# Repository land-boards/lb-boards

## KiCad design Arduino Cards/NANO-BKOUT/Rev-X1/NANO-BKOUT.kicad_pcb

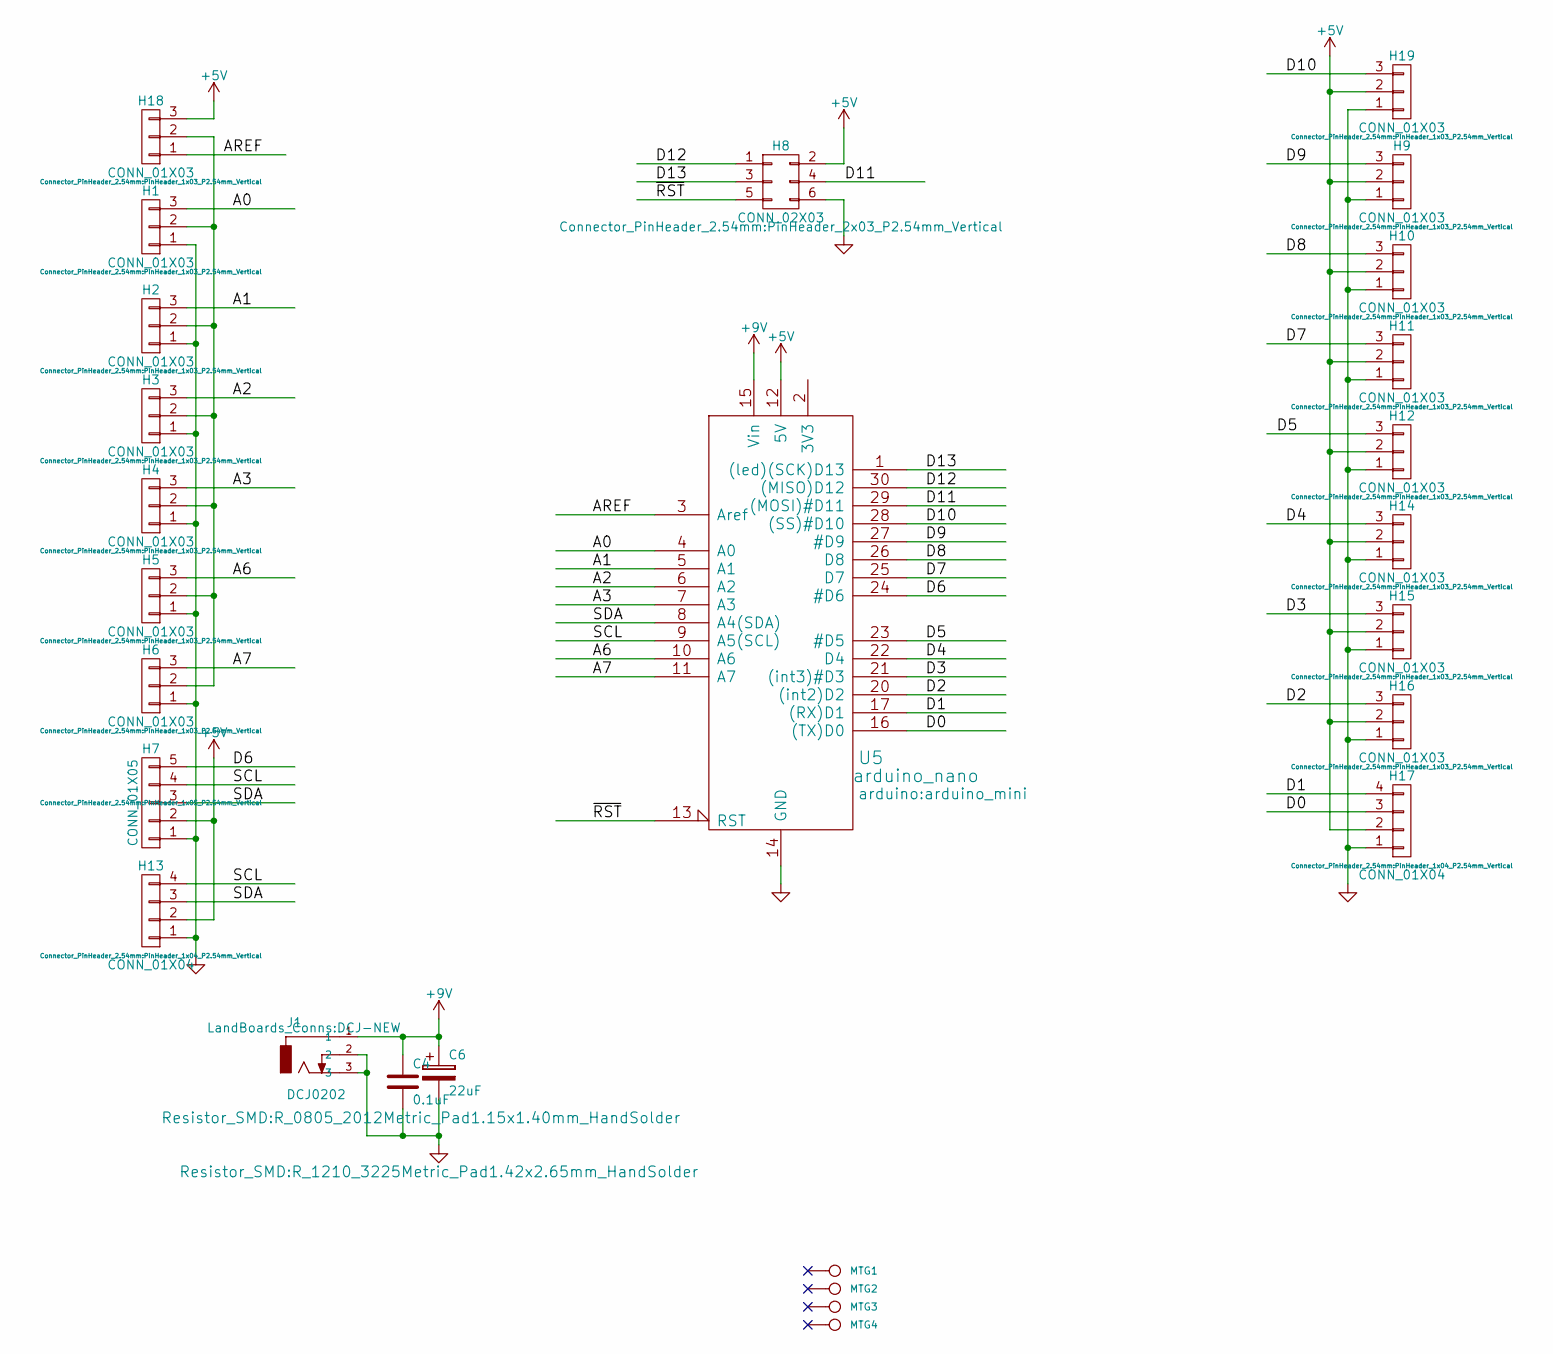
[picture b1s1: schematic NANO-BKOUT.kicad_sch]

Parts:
C4: 0.1uF; R_0805_2012Metric_Pad1.15x1.40mm_HandSolder
C6: 22uF; R_1210_3225Metric_Pad1.42x2.65mm_HandSolder
H1, H2, H3, H4, H5, H6, H9, H10, H11, H12, H14, H15, H16, H18, H19: CONN_01X03; PinHeader_1x03_P2.54mm_Vertical
H7: CONN_01X05; PinHeader_1x05_P2.54mm_Vertical
H8: CONN_02X03; PinHeader_2x03_P2.54mm_Vertical
H13, H17: CONN_01X04; PinHeader_1x04_P2.54mm_Vertical
J1: DCJ0202; DCJ-NEW
MTG1, MTG2, MTG3, MTG4: CONN_1; MTG-4-40
U5: arduino_nano; arduino_mini

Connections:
+5V: H7.2, H8.2, H9.2, H10.2, H11.2, H12.2, H13.2, H14.2, H15.2, H16.2, H17.2, H18.3, H19.2, U5.12 (5V)
+9V: C4.1, C6.1, J1.1, U5.15 (Vin)
/A0: H1.3, U5.4 (A0)
/A1: H2.3, U5.5 (A1)
/A2: H3.3, U5.6 (A2)
/A3: H4.3, U5.7 (A3)
/A6: H5.3, U5.10 (A6)
/A7: H6.3, U5.11 (A7)
/AREF: H18.1, U5.3 (Aref)
/D0: H17.3, U5.16 ((TX)D0)
/D1: H17.4, U5.17 ((RX)D1)
/D2: H16.3, U5.20 ((int2)D2)
/D3: H15.3, U5.21 ((int3)#D3)
/D4: H14.3, U5.22 (D4)
/D5: H12.3, U5.23 (#D5)
/D6: H7.5, U5.24 (#D6)
/D7: H11.3, U5.25 (D7)
/D8: H10.3, U5.26 (D8)
/D9: H9.3, U5.27 (#D9)
/D10: H19.3, U5.28 ((SS)#D10)
/D11: H8.4, U5.29 ((MOSI)#D11)
/D12: H8.1, U5.30 ((MISO)D12)
/D13: H8.3, U5.1 ((led)(SCK)D13)
/SCL: H7.4, H13.4, U5.9 (A5(SCL))
/SDA: H7.3, H13.3, U5.8 (A4(SDA))
/~RST: H8.5, U5.13 (RST)
GND: C4.2, C6.2, H1.1, H2.1, H3.1, H4.1, H5.1, H6.1, H7.1, H8.6, H9.1, H10.1, H11.1, H12.1, H13.1, H14.1, H15.1, H16.1, H17.1, H19.1, J1.2, J1.3, U5.14 (GND), U5.19 (GND)
unnamed: H1.2, H2.2, H3.2, H4.2, H5.2, H6.2, H18.2

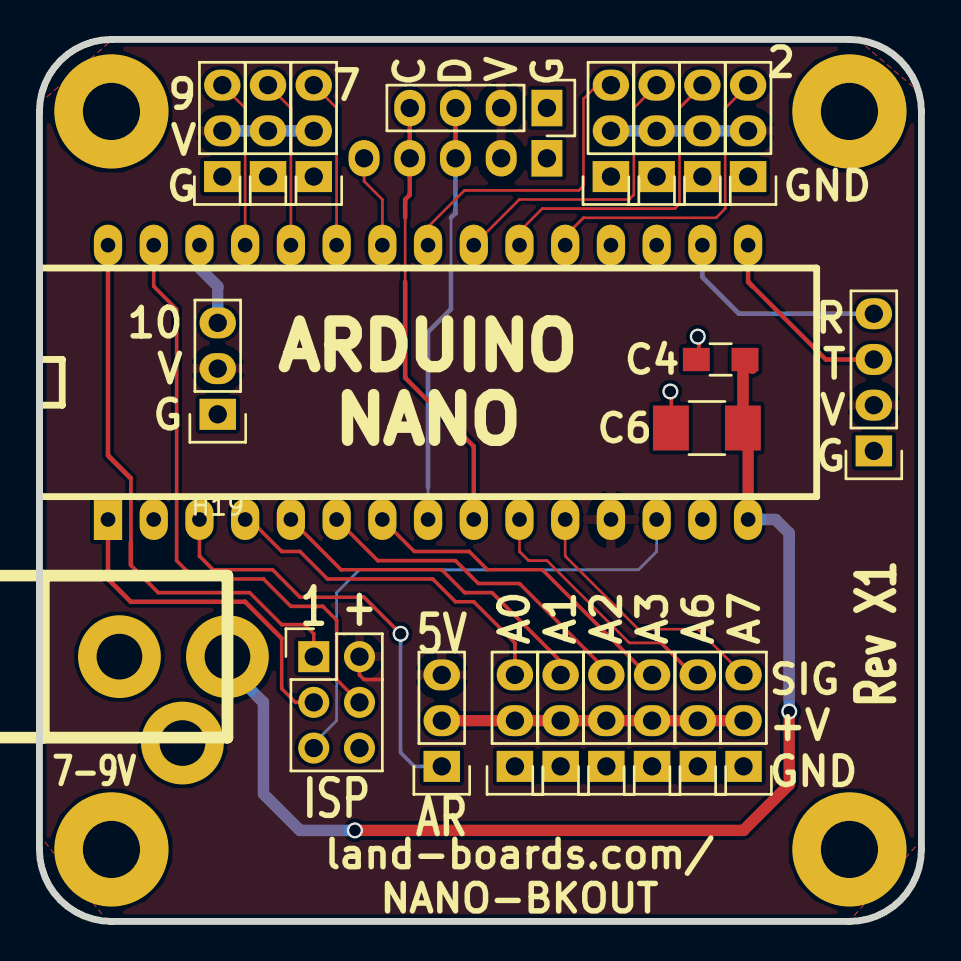
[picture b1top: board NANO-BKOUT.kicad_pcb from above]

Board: 2 copper layers, 49.0 x 49.0 mm, 27 parts (1 on the bottom side), 28 nets.

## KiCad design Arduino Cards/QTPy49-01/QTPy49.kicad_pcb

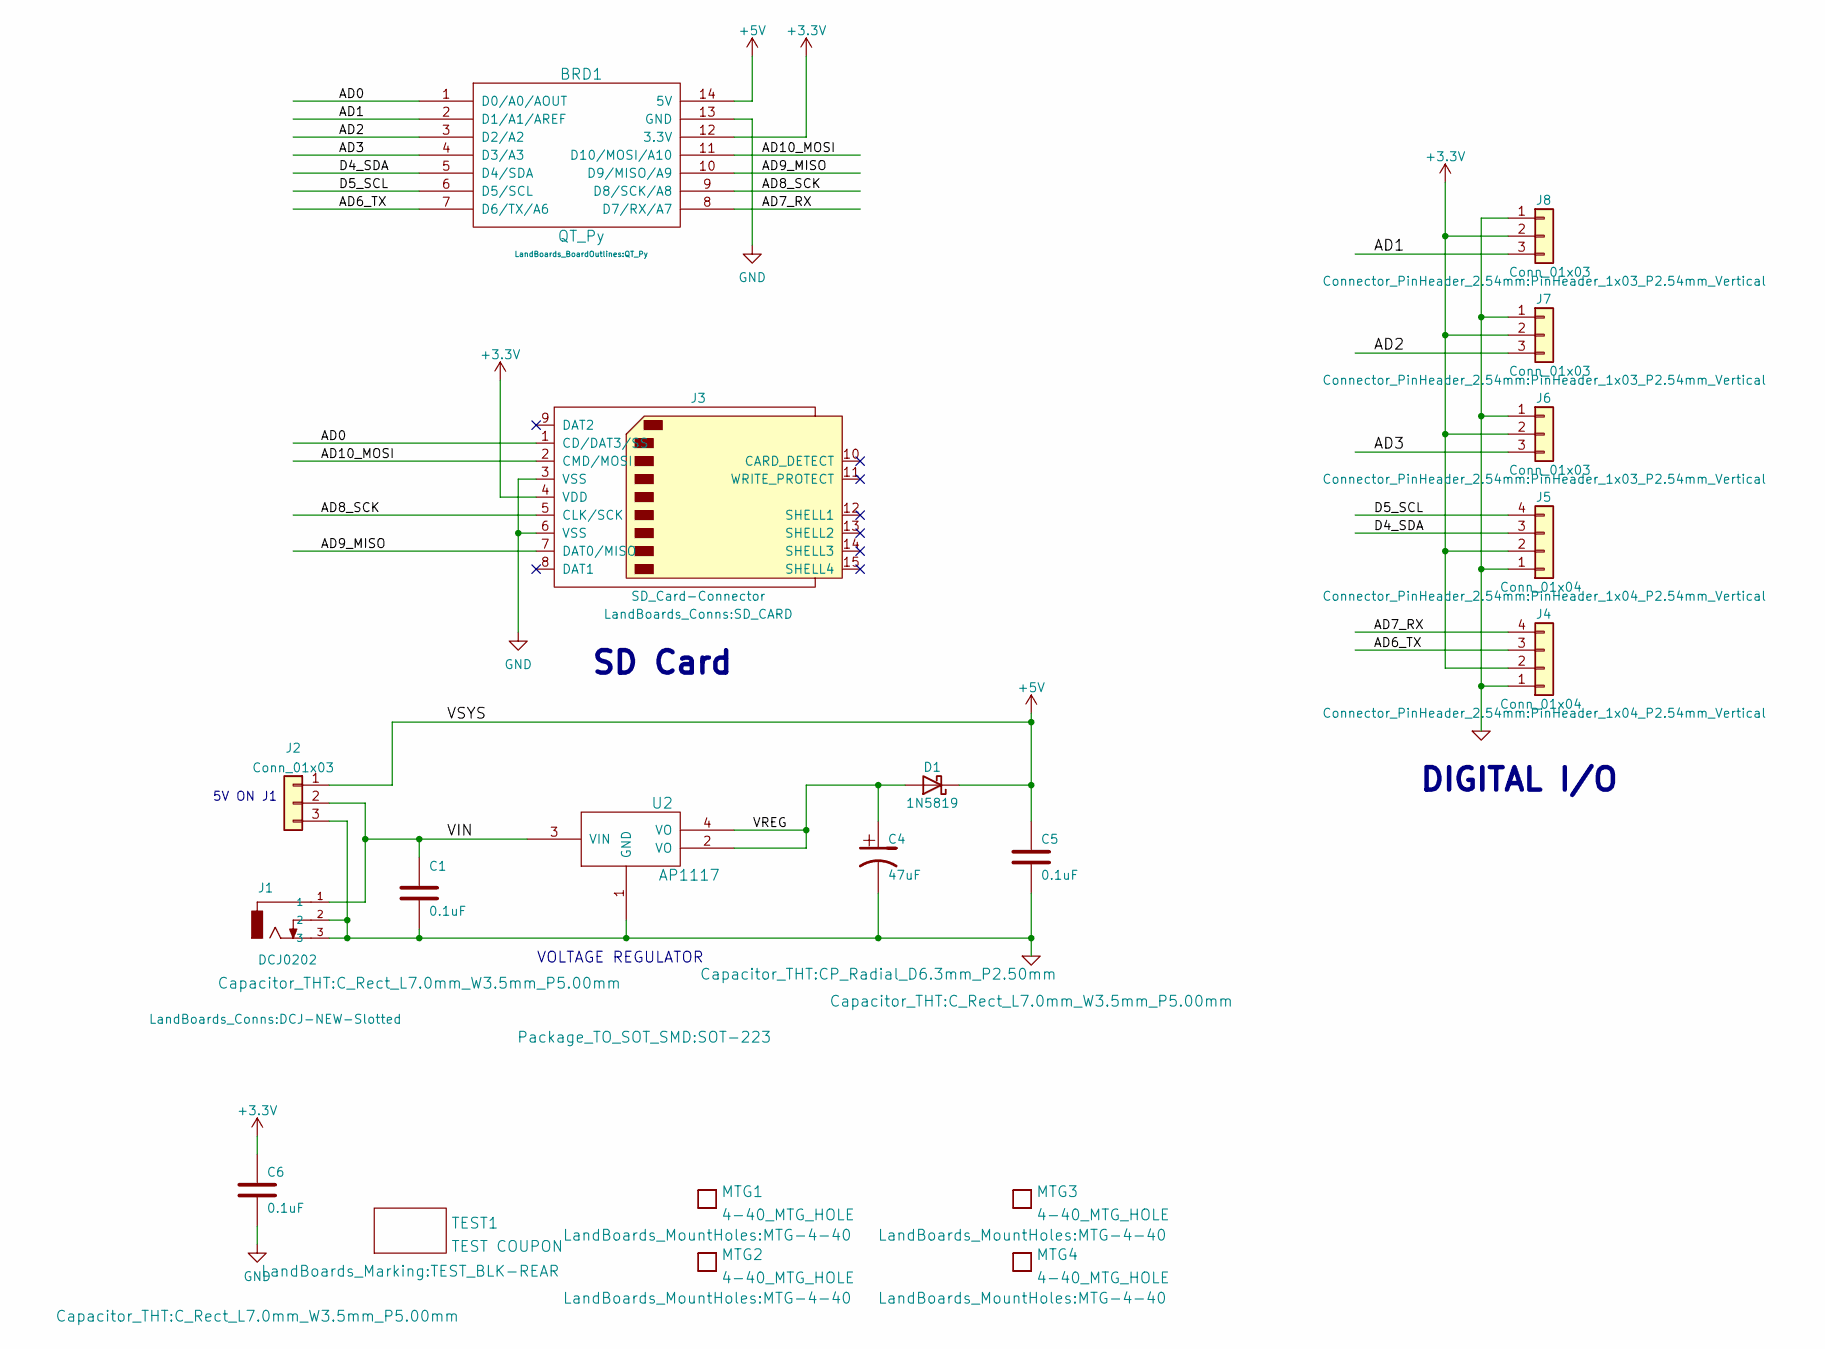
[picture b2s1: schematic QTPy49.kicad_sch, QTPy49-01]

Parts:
BRD1: QT_Py
C1, C5, C6: 0.1uF; C_Rect_L7.0mm_W3.5mm_P5.00mm
C4: 47uF; CP_Radial_D6.3mm_P2.50mm
D1: 1N5819; D_DO-41_SOD81_P10.16mm_Horizontal
J1: DCJ0202; DCJ-NEW-Slotted
J2, J6, J7, J8: Conn_01x03; PinHeader_1x03_P2.54mm_Vertical
J3: SD_Card-Connector; SD_CARD
J4, J5: Conn_01x04; PinHeader_1x04_P2.54mm_Vertical
MTG1, MTG2, MTG3, MTG4: 4-40_MTG_HOLE; MTG-4-40
TEST1: TEST COUPON; TEST_BLK-REAR
U2: AP1117; SOT-223

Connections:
+3V3: BRD1.12 (3.3V), C6.1, J3.4 (VDD), J4.2, J5.2, J6.2, J7.2, J8.2
+5V: BRD1.14 (5V), C5.1, D1.1 (K), J2.1
/AD0: BRD1.1 (D0/A0/AOUT), J3.1 (CD/DAT3/SS)
/AD1: BRD1.2 (D1/A1/AREF), J8.3
/AD2: BRD1.3 (D2/A2), J7.3
/AD3: BRD1.4 (D3/A3), J6.3
/AD6_TX: BRD1.7 (D6/TX/A6), J4.3
/AD7_RX: BRD1.8 (D7/RX/A7), J4.4
/AD8_SCK: BRD1.9 (D8/SCK/A8), J3.5 (CLK/SCK)
/AD9_MISO: BRD1.10 (D9/MISO/A9), J3.7 (DAT0/MISO)
/AD10_MOSI: BRD1.11 (D10/MOSI/A10), J3.2 (CMD/MOSI)
/D4_SDA: BRD1.5 (D4/SDA), J5.3
/D5_SCL: BRD1.6 (D5/SCL), J5.4
/VIN: C1.1, J1.1, J2.2, U2.3 (VIN)
/VREG: C4.1, D1.2 (A), U2.2 (VO), U2.4 (VO)
GND: BRD1.13 (GND), C1.2, C4.2, C5.2, C6.2, J1.2, J1.3, J2.3, J3.3 (VSS), J3.6 (VSS), J4.1, J5.1, J6.1, J7.1, J8.1, U2.1 (GND)

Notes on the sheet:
SD Card
DIGITAL I/O
5V ON J1
VOLTAGE REGULATOR

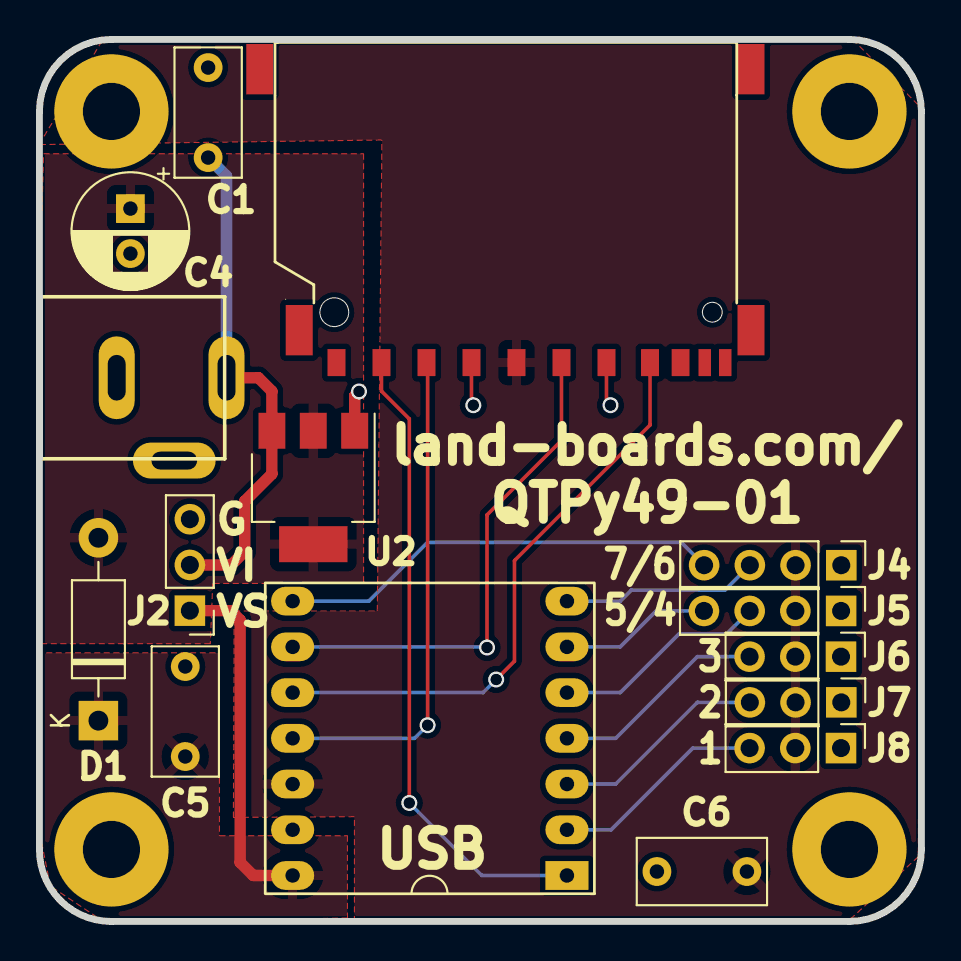
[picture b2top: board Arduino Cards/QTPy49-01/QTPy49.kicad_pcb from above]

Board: 2 copper layers, 49.0 x 49.0 mm, 20 parts (0 on the bottom side), 16 nets.

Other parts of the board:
TEST: TEST COUPON; TEST_BLK-REAR

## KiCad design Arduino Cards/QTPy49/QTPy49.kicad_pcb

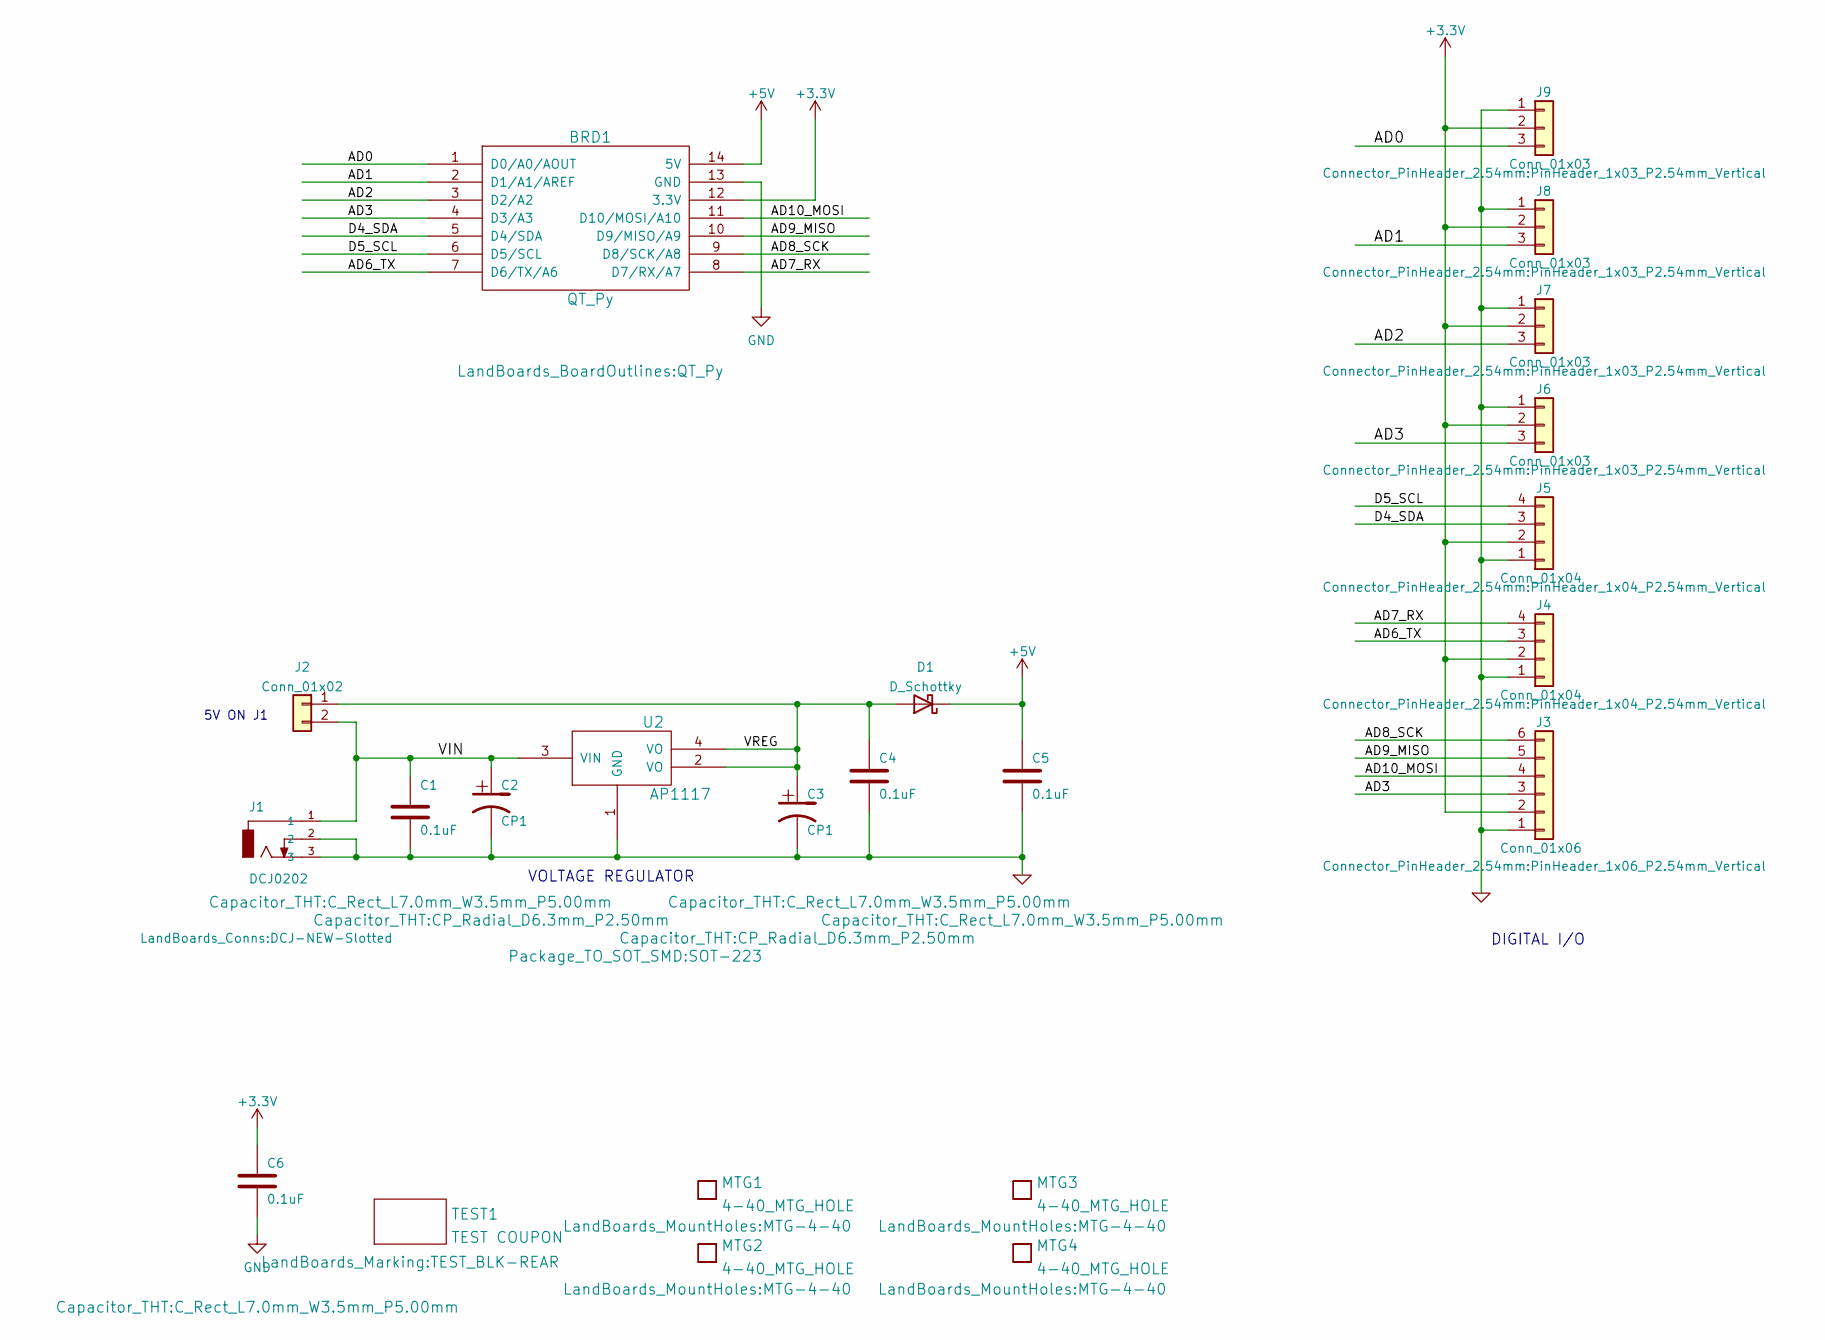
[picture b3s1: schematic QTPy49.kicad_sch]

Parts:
BRD1: QT_Py
C1, C4, C5, C6: 0.1uF; C_Rect_L7.0mm_W3.5mm_P5.00mm
C2, C3: CP1; CP_Radial_D6.3mm_P2.50mm
D1: D_Schottky; D_DO-41_SOD81_P10.16mm_Horizontal
J1: DCJ0202; DCJ-NEW-Slotted
J2: Conn_01x02; PinHeader_1x02_P2.54mm_Vertical
J3: Conn_01x06; PinHeader_1x06_P2.54mm_Vertical
J4, J5: Conn_01x04; PinHeader_1x04_P2.54mm_Vertical
J6, J7, J8, J9: Conn_01x03; PinHeader_1x03_P2.54mm_Vertical
MTG1, MTG2, MTG3, MTG4: 4-40_MTG_HOLE; MTG-4-40
TEST1: TEST COUPON; TEST_BLK-REAR
U2: AP1117; SOT-223

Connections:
+3V3: BRD1.12 (3.3V), C6.1, J3.2, J4.2, J5.2, J6.2, J7.2, J8.2, J9.2
+5V: BRD1.14 (5V), C5.1, D1.1 (K)
/AD0: BRD1.1 (D0/A0/AOUT), J9.3
/AD1: BRD1.2 (D1/A1/AREF), J8.3
/AD2: BRD1.3 (D2/A2), J7.3
/AD3: BRD1.4 (D3/A3), J3.3, J6.3
/AD6_TX: BRD1.7 (D6/TX/A6), J4.3
/AD7_RX: BRD1.8 (D7/RX/A7), J4.4
/AD8_SCK: BRD1.9 (D8/SCK/A8), J3.6
/AD9_MISO: BRD1.10 (D9/MISO/A9), J3.5
/AD10_MOSI: BRD1.11 (D10/MOSI/A10), J3.4
/D4_SDA: BRD1.5 (D4/SDA), J5.3
/D5_SCL: BRD1.6 (D5/SCL), J5.4
/VIN: C1.1, C2.1, J1.1, J2.2, U2.3 (VIN)
/VREG: C3.1, C4.1, D1.2 (A), J2.1, U2.2 (VO), U2.4 (VO)
GND: BRD1.13 (GND), C1.2, C2.2, C3.2, C4.2, C5.2, C6.2, J1.2, J1.3, J3.1, J4.1, J5.1, J6.1, J7.1, J8.1, J9.1, U2.1 (GND)

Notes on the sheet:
DIGITAL I/O
5V ON J1
VOLTAGE REGULATOR

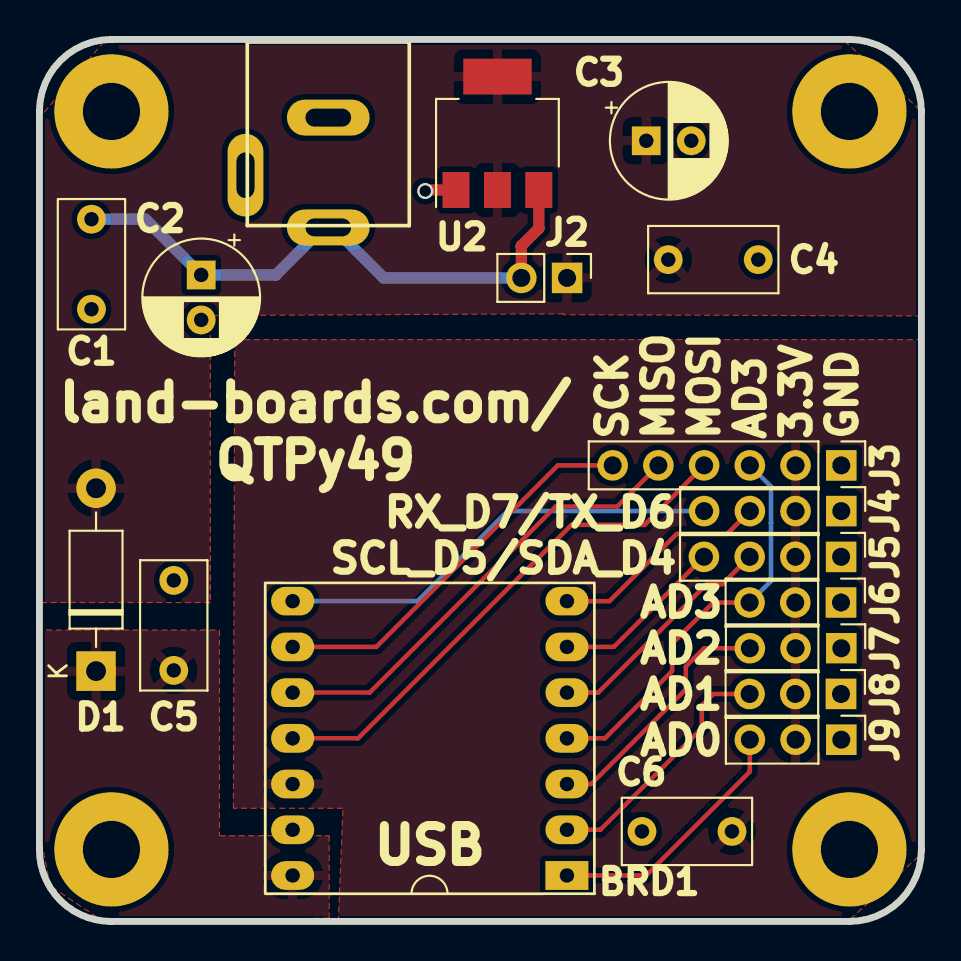
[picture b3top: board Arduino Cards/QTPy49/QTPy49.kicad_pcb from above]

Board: 2 copper layers, 49.0 x 49.0 mm, 23 parts (0 on the bottom side), 16 nets.

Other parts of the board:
TEST: TEST COUPON; TEST_BLK-REAR

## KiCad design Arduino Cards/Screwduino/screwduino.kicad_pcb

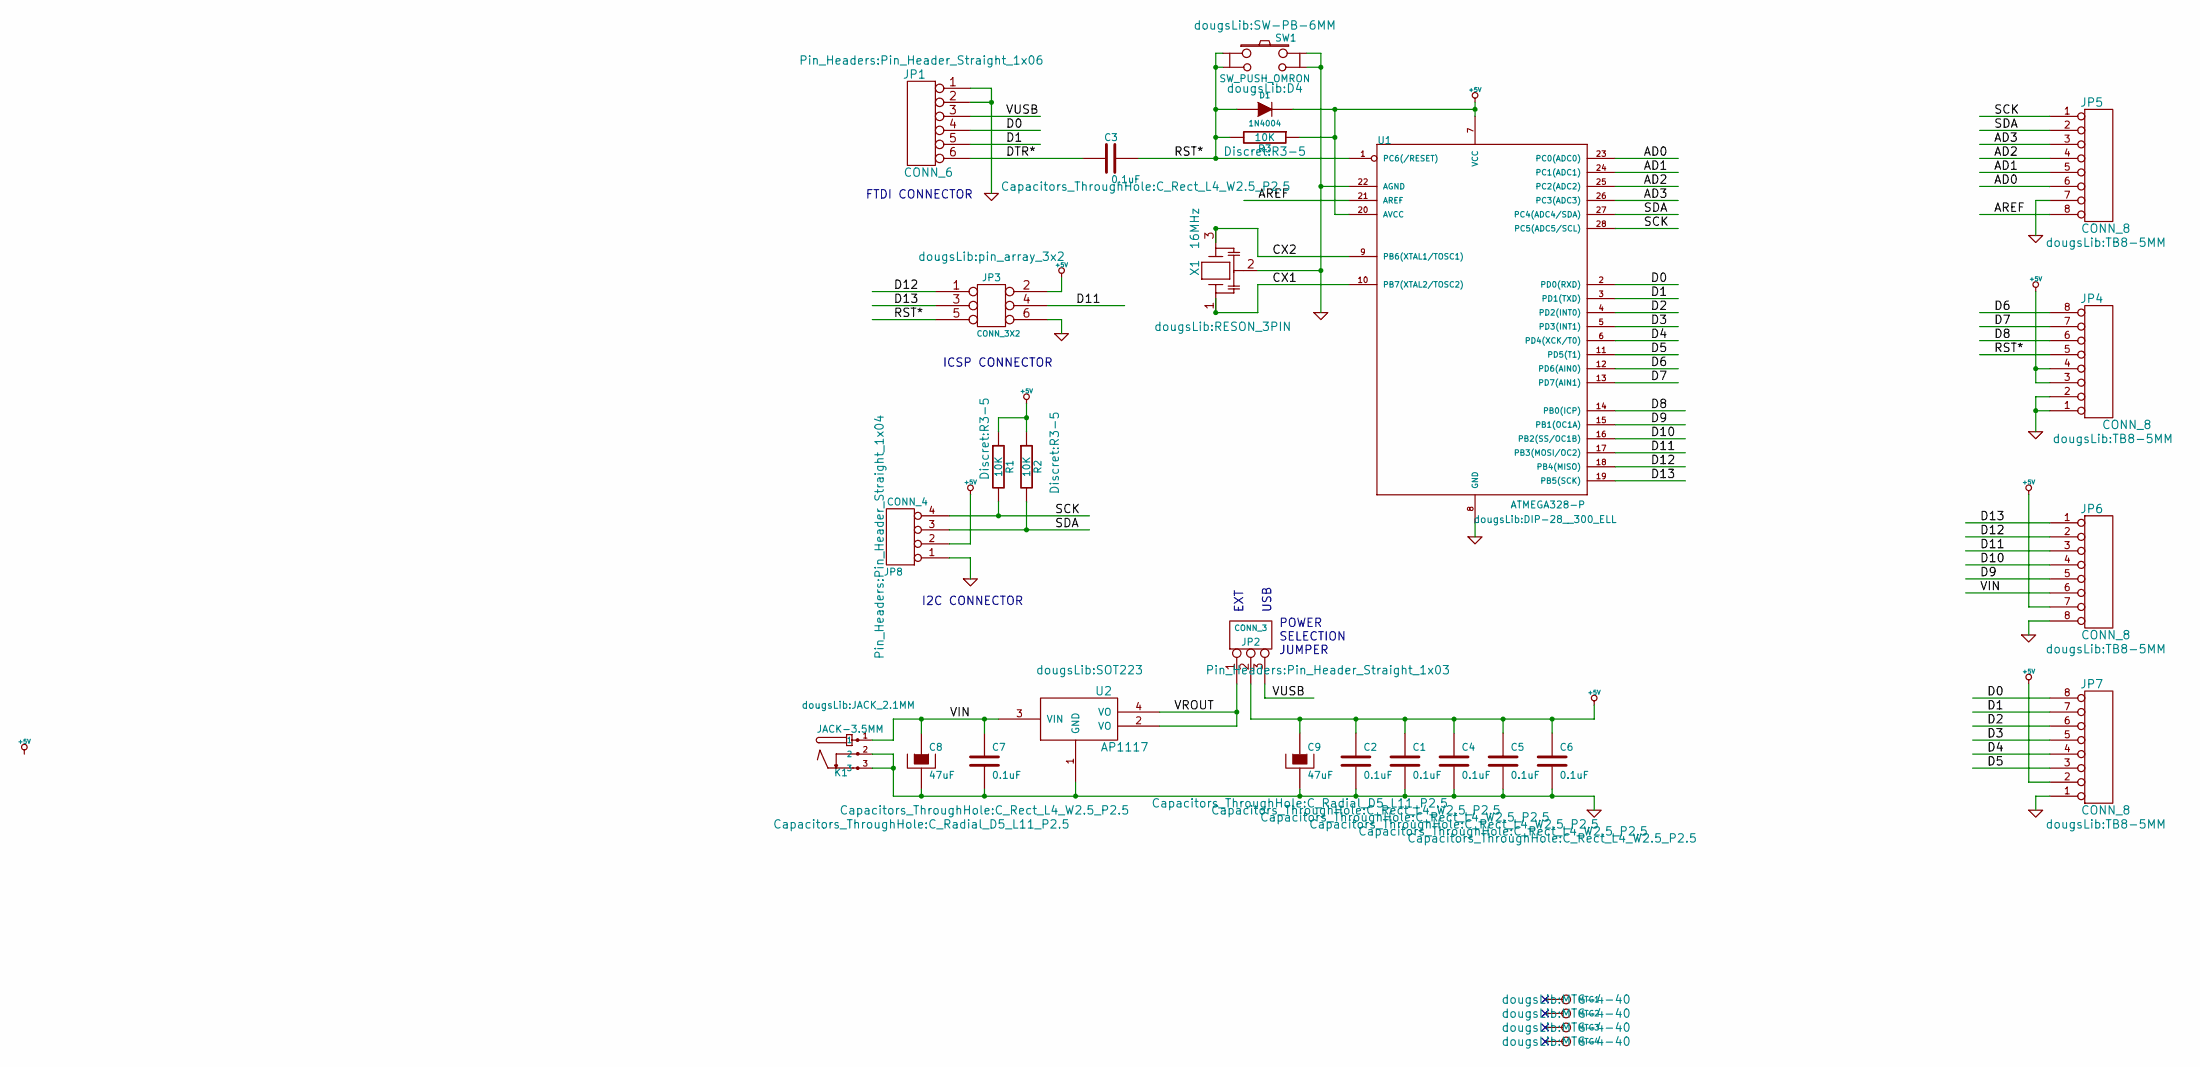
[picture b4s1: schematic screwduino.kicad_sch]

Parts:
C1, C2, C3, C4, C5, C6, C7: 0.1uF; C_Rect_L4_W2.5_P2.5; MfgPN 1C10Z5U104M050B
C8, C9: 47uF; C_Radial_D5_L11_P2.5; MfgPN REA100M1EBK-0511P
D1: 1N4004; D4; MfgPN 1N4004
JP1: CONN_6; Pin_Header_Straight_1x06; MfgPN 68602-406HLF
JP2: CONN_3; Pin_Header_Straight_1x03; MfgPN 69190-403
JP3: CONN_3X2; pin_array_3x2; MfgPN 929836-09-03
JP4, JP5, JP7: CONN_8; TB8-5MM; MfgPN 1935226
JP6: CONN_8; TB8-5MM; MfgPN 651-1935226
JP8: CONN_4; Pin_Header_Straight_1x04; MfgPN 68602-404HLF
K1: JACK-3.5MM; JACK_2.1MM; MfgPN 163-179PH-EX
MTG1, MTG2, MTG3, MTG4: CONN_1; MTG-4-40
R1, R2, R3: 10K; R3-5; MfgPN CMF5510K000FKEK
SW1: SW_PUSH_OMRON; SW-PB-6MM; MfgPN TL1105DF100Q
U1: ATMEGA328-P; DIP-28__300_ELL; MfgPN ATMEGA328P-PU
U2: AP1117; SOT223; MfgPN TLV1117-50CDCYR
X1: 16MHz; RESON_3PIN; MfgPN CSTLS16M0X51-A0

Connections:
+5V: C1.1, C2.1, C4.1, C5.1, C6.1, C9.1, D1.2 (K), JP2.2 (PM), JP3.2, JP4.3, JP4.4, JP6.7, JP7.2, JP8.2, R1.1, R2.1, R3.1, U1.7 (VCC), U1.20 (AVCC)
/AD0: JP5.6, U1.23 (PC0(ADC0))
/AD1: JP5.5, U1.24 (PC1(ADC1))
/AD2: JP5.4, U1.25 (PC2(ADC2))
/AD3: JP5.3, U1.26 (PC3(ADC3))
/AREF: JP5.8, U1.21 (AREF)
/CX1: U1.10 (PB7(XTAL2/TOSC2)), X1.1
/CX2: U1.9 (PB6(XTAL1/TOSC1)), X1.3
/D0: JP1.4, JP7.8, U1.2 (PD0(RXD))
/D1: JP1.5, JP7.7, U1.3 (PD1(TXD))
/D2: JP7.6, U1.4 (PD2(INT0))
/D3: JP7.5, U1.5 (PD3(INT1))
/D4: JP7.4, U1.6 (PD4(XCK/T0))
/D5: JP7.3, U1.11 (PD5(T1))
/D6: JP4.8, U1.12 (PD6(AIN0))
/D7: JP4.7, U1.13 (PD7(AIN1))
/D8: JP4.6, U1.14 (PB0(ICP))
/D9: JP6.5, U1.15 (PB1(OC1A))
/D10: JP6.4, U1.16 (PB2(SS/OC1B))
/D11: JP3.4, JP6.3, U1.17 (PB3(MOSI/OC2))
/D12: JP3.1, JP6.2, U1.18 (PB4(MISO))
/D13: JP3.3, JP6.1, U1.19 (PB5(SCK))
/DTR*: C3.2, JP1.6
/RST*: C3.1, D1.1 (A), JP3.5, JP4.5, R3.2, SW1.1, SW1.2, U1.1 (PC6(/RESET))
/SCK: JP5.1, JP8.4, R1.2, U1.28 (PC5(ADC5/SCL))
/SDA: JP5.2, JP8.3, R2.2, U1.27 (PC4(ADC4/SDA))
/VIN: C7.1, C8.1, JP6.6, K1.1, U2.3 (VIN)
/VROUT: JP2.1, U2.2 (VO), U2.4 (VO)
/VUSB: JP1.3, JP2.3
GND: C1.2, C2.2, C4.2, C5.2, C6.2, C7.2, C8.2, C9.2, JP1.1, JP1.2, JP3.6, JP4.1, JP4.2, JP5.7, JP6.8, JP7.1, JP8.1, K1.2, K1.3, SW1.3, SW1.4, U1.8 (GND), U1.22 (AGND), U2.1 (GND), X1.2

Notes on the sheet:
USB
ICSP CONNECTOR
EXT
POWER SELECTION JUMPER
FTDI CONNECTOR
I2C CONNECTOR

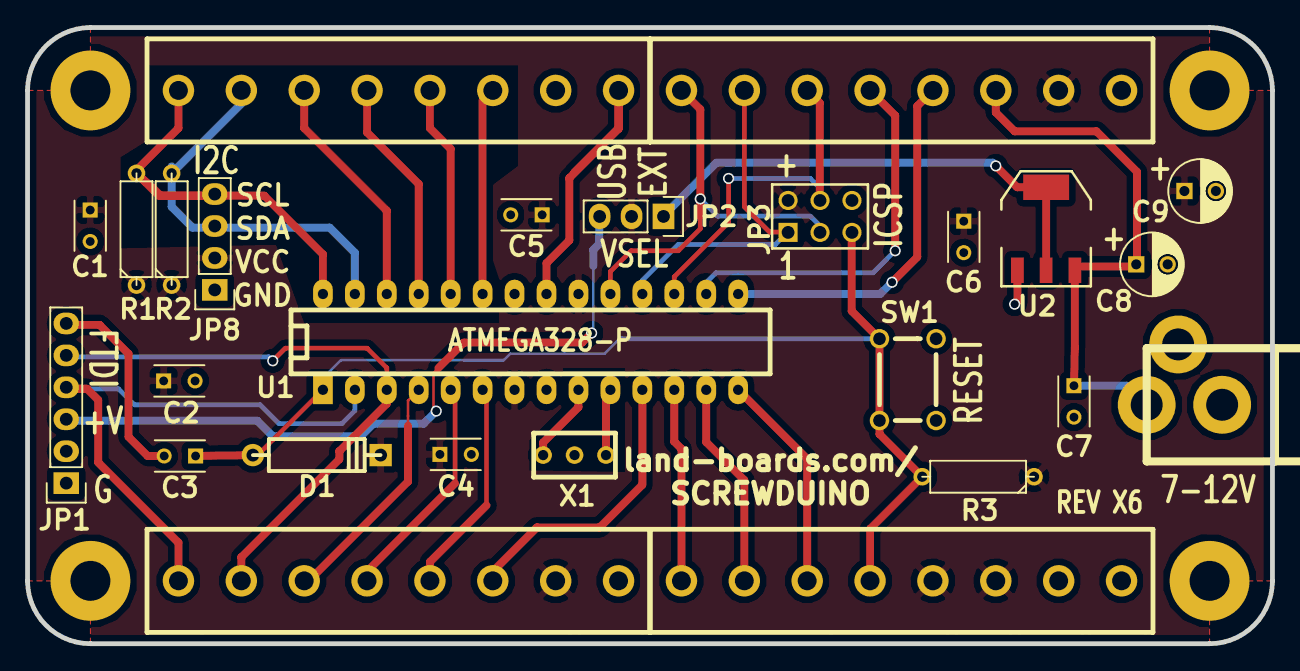
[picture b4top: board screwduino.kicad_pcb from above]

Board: 2 copper layers, 99.0 x 49.0 mm, 31 parts (0 on the bottom side), 30 nets.

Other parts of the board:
TESTED: VAL**; TEST_BLK-REAR

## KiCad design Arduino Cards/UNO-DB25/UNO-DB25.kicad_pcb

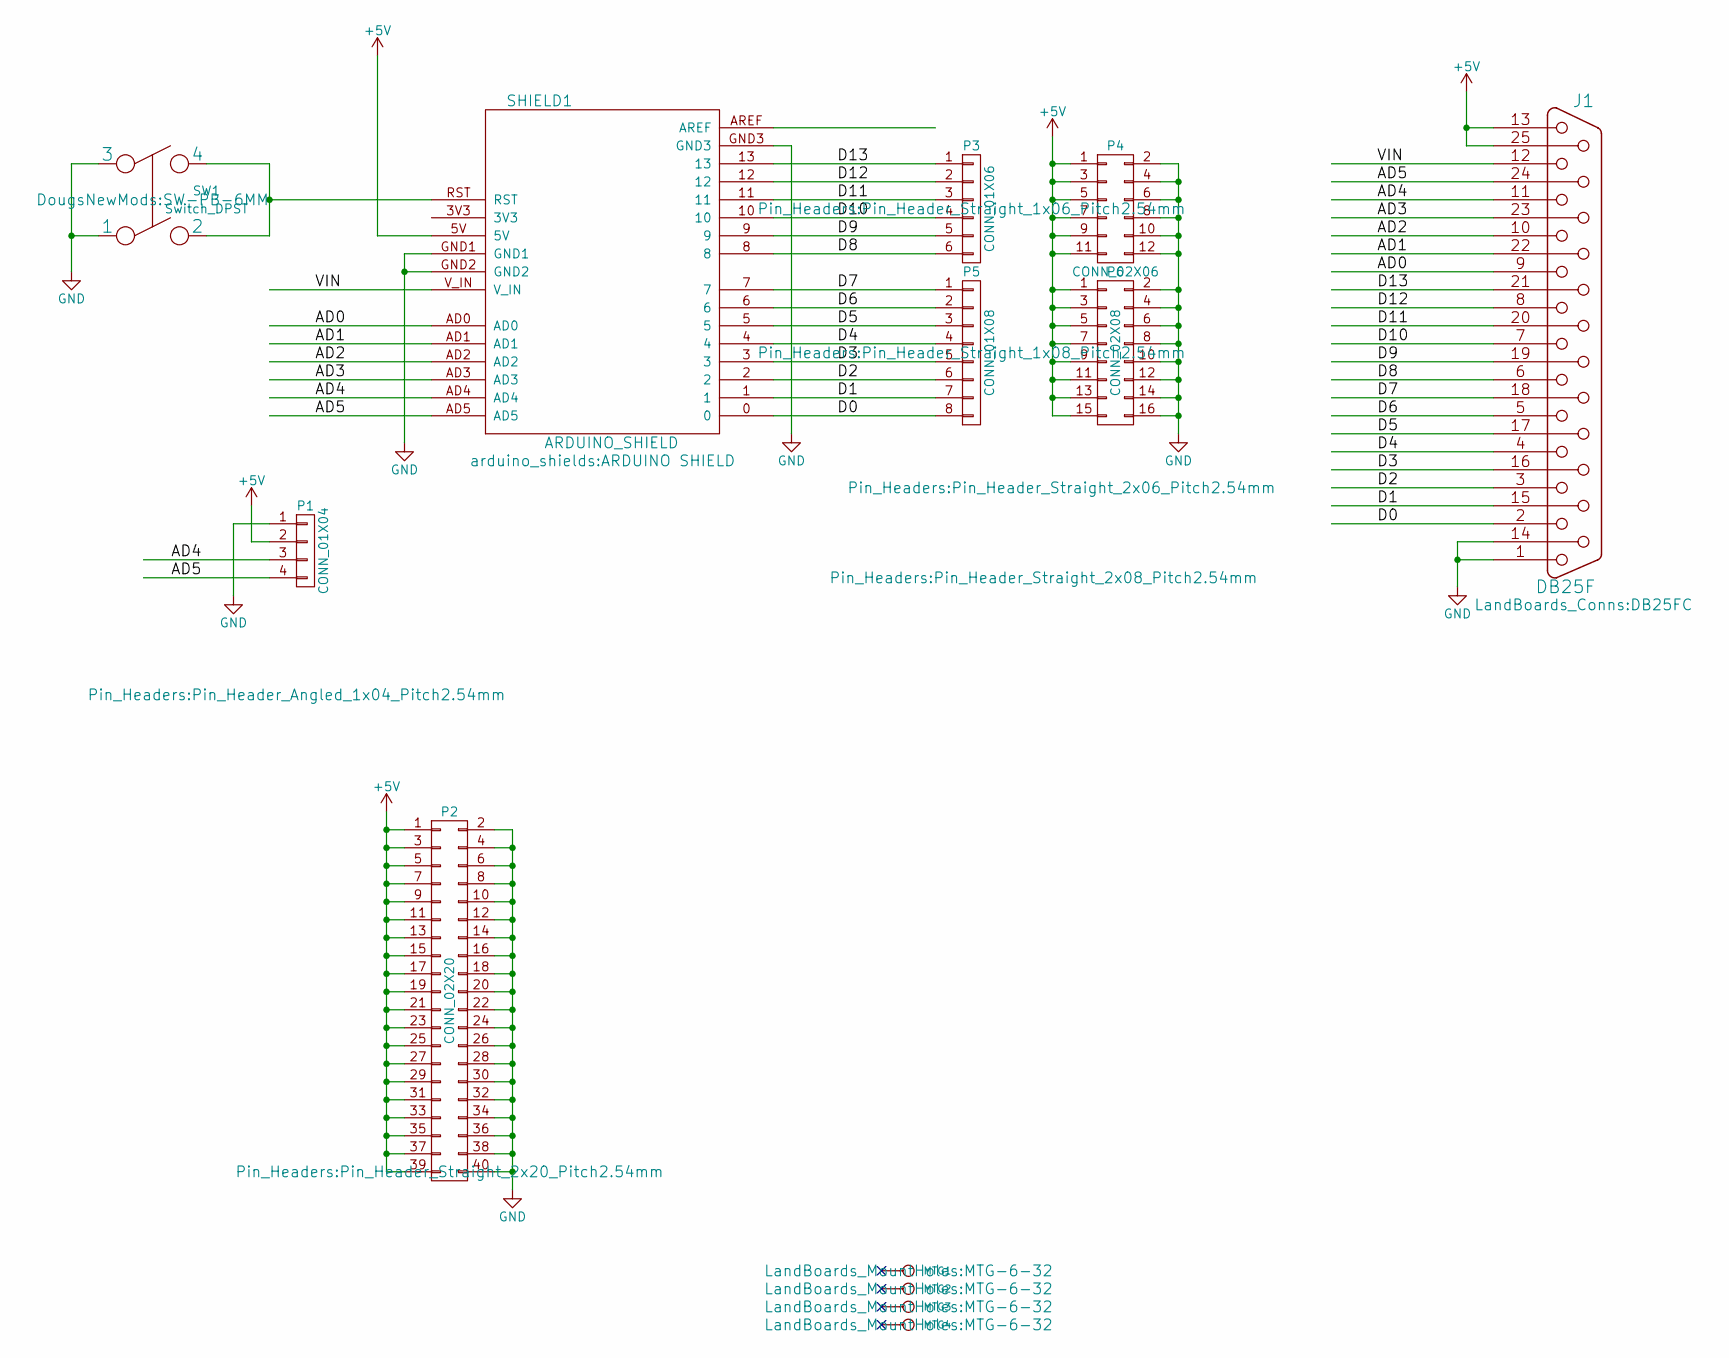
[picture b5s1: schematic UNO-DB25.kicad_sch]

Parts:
J1: DB25F; DB25FC
MTG1, MTG2, MTG3, MTG4: CONN_1; MTG-6-32
P1: CONN_01X04; Pin_Header_Angled_1x04_Pitch2.54mm
P2: CONN_02X20; Pin_Header_Straight_2x20_Pitch2.54mm
P3: CONN_01X06; Pin_Header_Straight_1x06_Pitch2.54mm
P4: CONN_02X06; Pin_Header_Straight_2x06_Pitch2.54mm
P5: CONN_01X08; Pin_Header_Straight_1x08_Pitch2.54mm
P6: CONN_02X08; Pin_Header_Straight_2x08_Pitch2.54mm
SHIELD1: ARDUINO_SHIELD; ARDUINO SHIELD
SW1: Switch_DPST; SW-PB-6MM

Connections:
+5V: J1.13, J1.25, P1.2, P2.1, P2.3, P2.5, P2.7, P2.9, P2.11, P2.13, P2.15, P2.17, P2.19, P2.21, P2.23, P2.25, P2.27, P2.29, P2.31, P2.33, P2.35, P2.37, P2.39, P4.1, P4.3, P4.5, P4.7, P4.9, P4.11, P6.1, P6.3, P6.5, P6.7, P6.9, P6.11, P6.13, P6.15, SHIELD1.5V
/AD0: J1.9, SHIELD1.AD0
/AD1: J1.22, SHIELD1.AD1
/AD2: J1.10, SHIELD1.AD2
/AD3: J1.23, SHIELD1.AD3
/AD4: J1.11, P1.3, SHIELD1.AD4
/AD5: J1.24, P1.4, SHIELD1.AD5
/D0: J1.2, P5.8, SHIELD1.0
/D1: J1.15, P5.7, SHIELD1.1
/D2: J1.3, P5.6, SHIELD1.2
/D3: J1.16, P5.5, SHIELD1.3
/D4: J1.4, P5.4, SHIELD1.4
/D5: J1.17, P5.3, SHIELD1.5
/D6: J1.5, P5.2, SHIELD1.6
/D7: J1.18, P5.1, SHIELD1.7
/D8: J1.6, P3.6, SHIELD1.8
/D9: J1.19, P3.5, SHIELD1.9
/D10: J1.7, P3.4, SHIELD1.10
/D11: J1.20, P3.3, SHIELD1.11
/D12: J1.8, P3.2, SHIELD1.12
/D13: J1.21, P3.1, SHIELD1.13
/VIN: J1.12, SHIELD1.V_IN
GND: J1.1, J1.14, P1.1, P2.2, P2.4, P2.6, P2.8, P2.10, P2.12, P2.14, P2.16, P2.18, P2.20, P2.22, P2.24, P2.26, P2.28, P2.30, P2.32, P2.34, P2.36, P2.38, P2.40, P4.2, P4.4, P4.6, P4.8, P4.10, P4.12, P6.2, P6.4, P6.6, P6.8, P6.10, P6.12, P6.14, P6.16, SHIELD1.GND1, SHIELD1.GND2, SHIELD1.GND3, SW1.1, SW1.3
unnamed: SHIELD1.RST, SW1.2, SW1.4

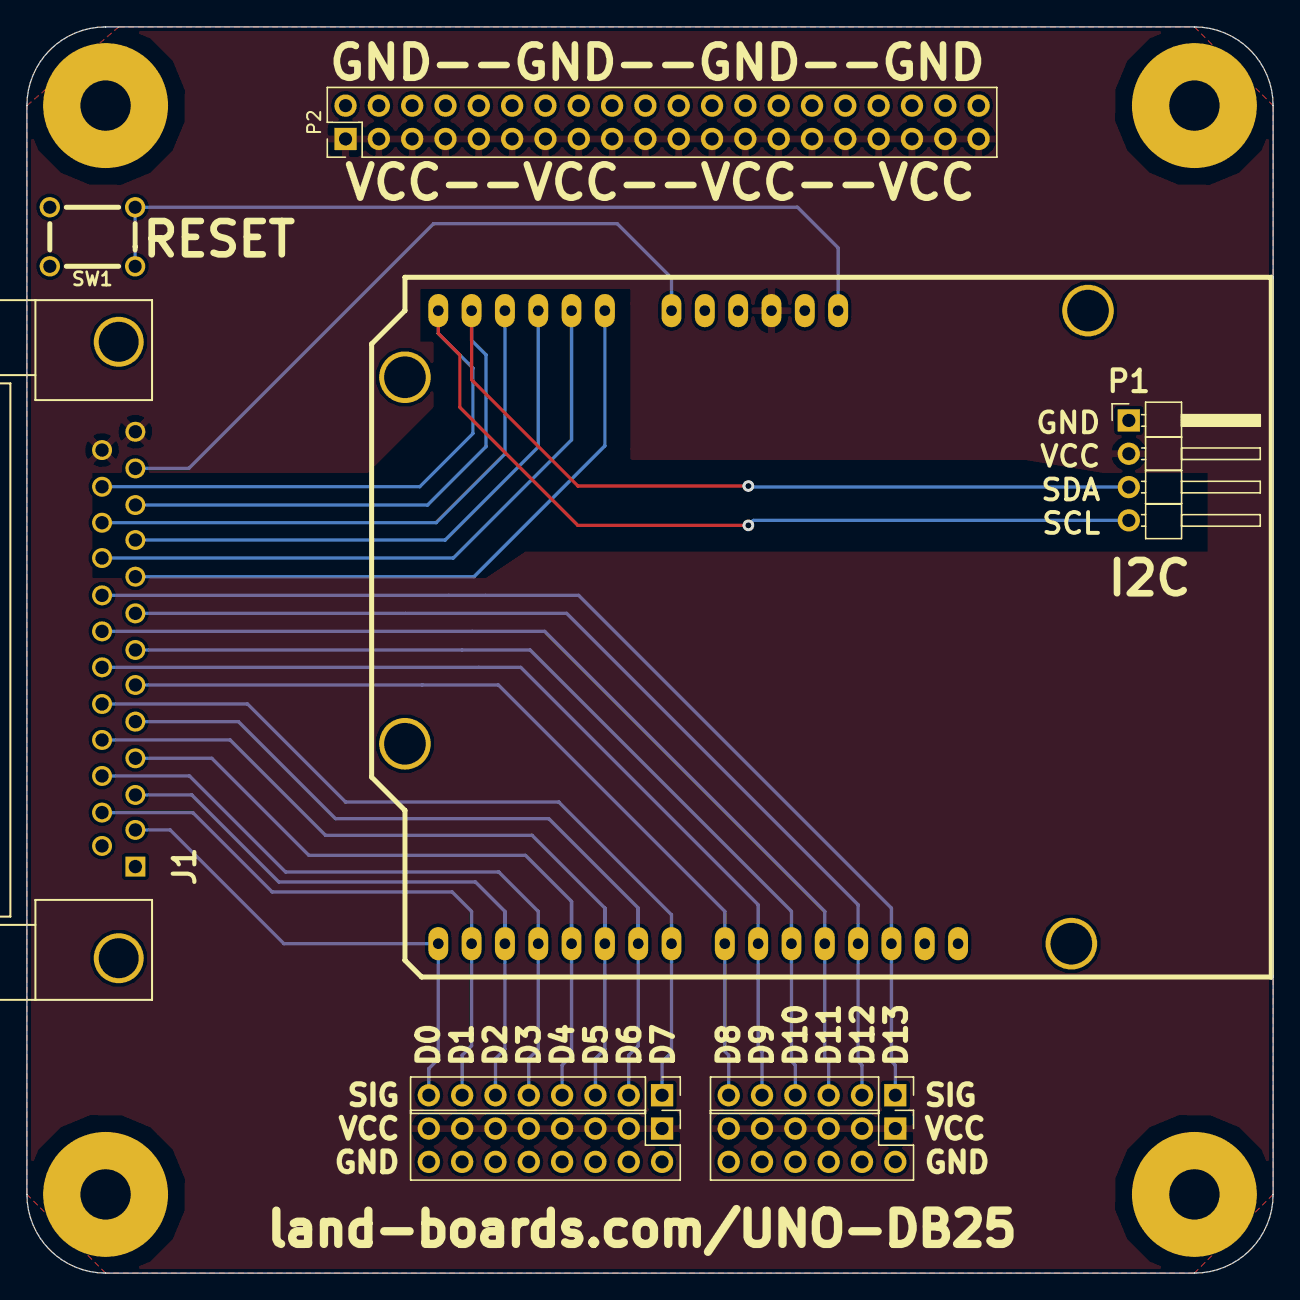
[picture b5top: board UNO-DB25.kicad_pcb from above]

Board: 2 copper layers, 95.0 x 95.0 mm, 13 parts (0 on the bottom side), 24 nets.
